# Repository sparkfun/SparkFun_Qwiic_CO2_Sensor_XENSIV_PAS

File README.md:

SparkFun Photoacoustic Spectroscopy CO2 Sensor - PASCO2V01 (Qwiic) 
========================================

[*SparkFun Photoacoustic Spectroscopy CO2 Sensor - PASCO2V01 (Qwiic) (SEN-22956)*](https://www.sparkfun.com/products/22956)

The SparkFun Photoacoustic Spectroscopy CO<sub>2</sub> Sensor features the XENSIV<sup>&trade;</sup> PASCO2V01 sensor package from Infineon<sup>&copy;</sup>. The sensor measures highly-accurate CO<sub>2</sub> data in direct parts-per-million (ppm) format over I<sup>2</sup>C, UART and PWM. The PAS CO2 employs a photoacoustic spectroscopy measurement system that combines narrow-band filtered IR light and a highly sensitive microphone inside the sensing cavity to measure CO<sub>2</sub> concentrations from 0 to 32,000 ppm with a best accuracy of &plusmn;(30ppm + 3%) when reading between 400 ppm and 5,000 ppm. It also includes a microcontroller that converts the data into direct ppm readout over any of the three communication interfaces. The IR emitter on the PAS CO2 requires a 12V supply so the board includes a AP3012 boost regulator with a series of decoupling capacitors to output a clean 12V from the 3.3V sourced through a Qwiic connection.

Repository Contents
-------------------

* **/Documentation** - Data sheets, additional product information
* **/Firmware** - Example code 
* **/Hardware** - Eagle design files (.brd, .sch)
* **/Production** - Production panel files (.brd)
* **/docs** -  Documentation files for the Photoacoustic Spectroscopy CO2 Sensor - PASCO2V01 (Qwiic) 

Documentation
--------------
* **[Library](https://github.com/Infineon/arduino-pas-co2-sensor)** - Arduino library for the XENSIV PAS CO2 Sensor.
* **[Hookup Guide](https://sparkfun.github.io/SparkFun_Qwiic_CO2_Sensor_XENSIV_PAS)** - Basic hookup guide for the Photoacoustic Spectroscopy CO2 Sensor - PASCO2V01 (Qwiic).

Product Versions
----------------
* [SEN-22956](https://www.sparkfun.com/products/22956) - Initial release of the SparkFun Photoacoustic Spectroscopy CO2 Sensor - PASCO2V01 (Qwiic) 

License Information
-------------------

This product is _**open source**_! 

Please review the LICENSE.md file for license information. 

If you have any questions or concerns on licensing, please contact technical support on our [SparkFun forums](https://forum.sparkfun.com/viewforum.php?f=152).

Distributed as-is; no warranty is given.

- Your friends at SparkFun.

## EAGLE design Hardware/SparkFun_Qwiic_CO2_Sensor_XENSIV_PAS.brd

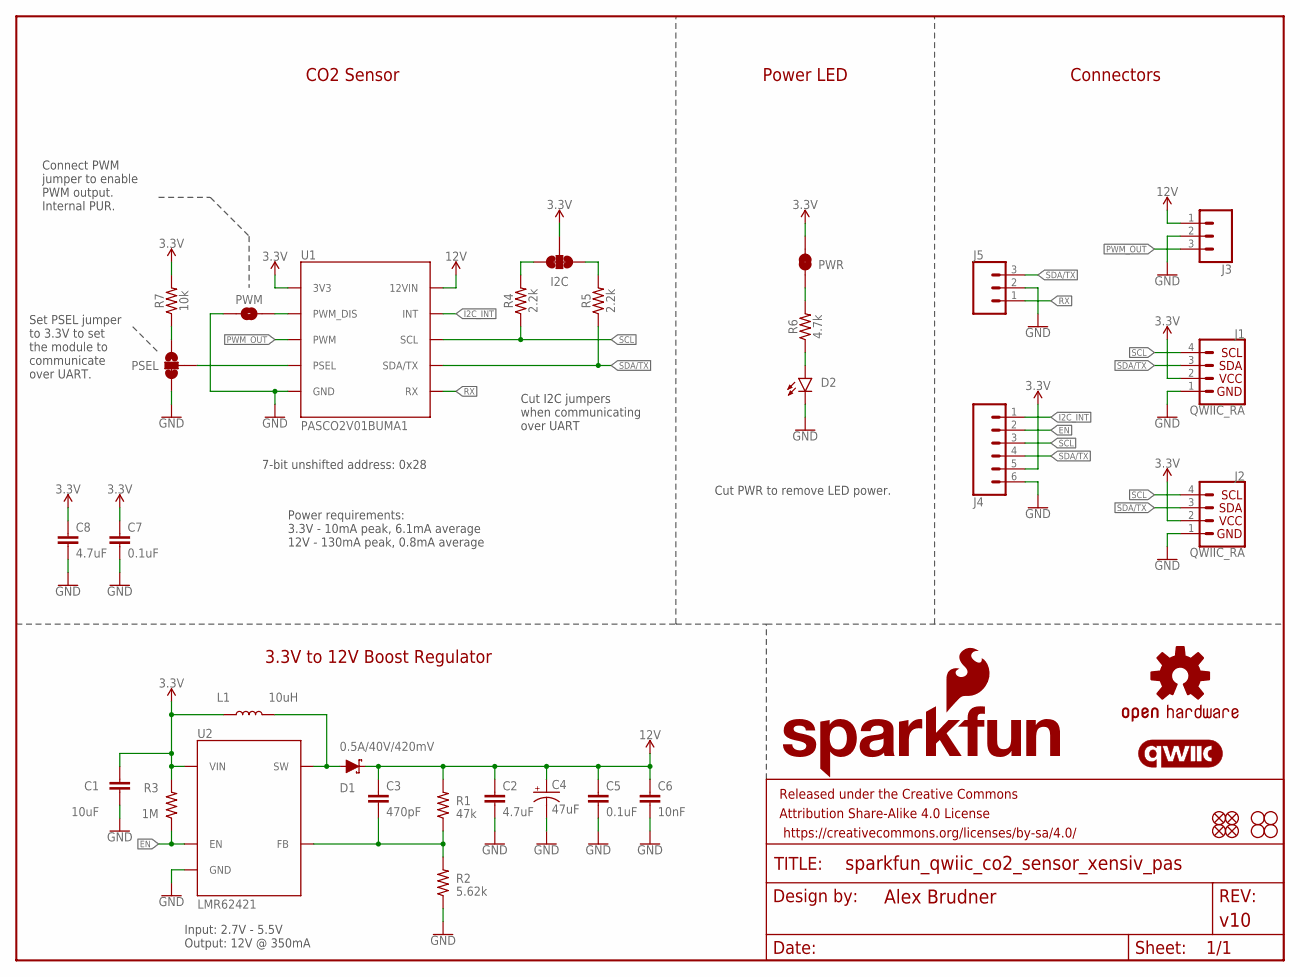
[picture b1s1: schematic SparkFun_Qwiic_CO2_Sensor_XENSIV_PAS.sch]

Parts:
C1: 10uF; 0805
C2, C8: 4.7uF; 0603
C3: 470pF; 0603
C4: 47uF; PANASONIC_D
C5, C7: 0.1uF; 0603
C6: 10nF; 0603
D1: 0.5A/40V/420mV; SOD-323
D2: LED-RED_0603-KB; LED-0603
FD1, FD2, FD3, FD4: FIDUCIALUFIDUCIAL; FIDUCIAL-MICRO
FRAME1: FRAME-LETTER; CREATIVE_COMMONS
H1, H2, H3, H4: STAND-OFF
I2C: JUMPER-SMT_3_2-NC_TRACE_SILK; SMT-JUMPER_3_2-NC_TRACE_SILK
J1, J2: QWIIC_RA; JST04_1MM_RA
J3, J5: CONN_031X03_NO_SILK; 1X03_NO_SILK
J4: CONN_06NO_SILK_NO_POP; 1X06_NO_SILK
L1: 10uH; 0805
LOGO1: SFE_LOGO_NAME_FLAME.1_INCH; SFE_LOGO_NAME_FLAME_.1
LOGO2: QWIIC_LOGO_5MM; QWIIC_5MM
LOGO3: OSHW-LOGOMINI; OSHW-LOGO-MINI
PSEL: JUMPER-SMT_3_1-NC_TRACE_SILK; SMT-JUMPER_3_1-NC_TRACE_SILK
PWM: JUMPER-SMT_2_NO_SILK; SMT-JUMPER_2_NO_SILK
PWR: JUMPER-SMT_2_NC_TRACE_SILK; SMT-JUMPER_2_NC_TRACE_SILK
R1: 47k; 0603
R2: 5.62k; 0603
R3: 1M; 0603
R4, R5: 2.2k; 0603
R6: 4.7k; 0603
R7: 10k; 0603
U1: PASCO2V01BUMA1; LG-MLGA-14-1_Z8B00206105
U2: LMR62421; SOT95P280X145-5M

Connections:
3.3V: C1.1, C7.1, C8.1, I2C.2, J1.2, J2.2, J4.5, L1.1, PWR.2, R3.2, R7.2, U1.1 (3V3), U2.5 (VIN)
12V: C2.1, C3.1, C4.+, C5.1, C6.1, D1.C, J3.1, R1.2, U1.10 (12VIN)
EN: J4.2, R3.1, U2.4 (EN)
GND: C1.2, C2.2, C4.-, C5.2, C6.2, C7.2, C8.2, D2.C, J1.1, J2.1, J3.2, J4.6, J5.2, PSEL.3, PWM.1, R2.1, U1.6 (GND), U1.11 (GND), U1.12 (GND), U1.13 (GND), U1.14 (GND), U2.2 (GND)
I2C_INT: J4.1, U1.7 (INT)
unnamed: I2C.1, R5.2
unnamed: D1.A, L1.2, U2.1 (SW)
unnamed: I2C.3, R4.2
unnamed: C3.2, R1.1, R2.2, U2.3 (FB)
unnamed: PSEL.2, U1.8 (PSEL)
unnamed: D2.A, R6.1
unnamed: PWR.1, R6.2
unnamed: PSEL.1, R7.1
unnamed: PWM.2, U1.5 (PWM_DIS)
PWM_OUT: J3.3, U1.9 (PWM)
RX: J5.1, U1.2 (RX)
SCL: J1.4, J2.4, J4.3, R4.1, U1.3 (SCL)
SDA/TX: J1.3, J2.3, J4.4, J5.3, R5.1, U1.4 (SDA/TX)

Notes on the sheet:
3.3V to 12V Boost Regulator
CO2 Sensor
Connectors
Set PSEL jumper to 3.3V to set the module to communicate over UART.
Cut I2C jumpers when communicating over UART
Power LED
Cut PWR to remove LED power.
Input: 2.7V - 5.5V Output: 12V @ 350mA
7-bit unshifted address: 0x28
Power requirements: 3.3V - 10mA peak, 6.1mA average 12V - 130mA peak, 0.8mA average
Connect PWM jumper to enable PWM output. Internal PUR.

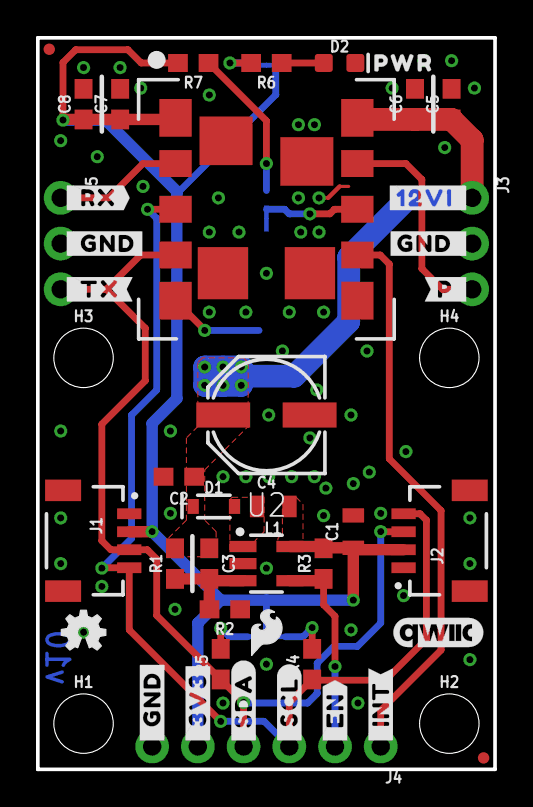
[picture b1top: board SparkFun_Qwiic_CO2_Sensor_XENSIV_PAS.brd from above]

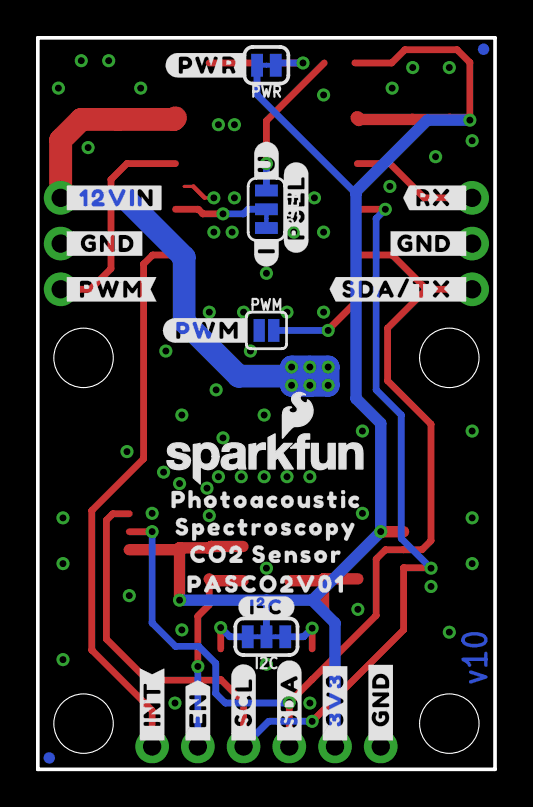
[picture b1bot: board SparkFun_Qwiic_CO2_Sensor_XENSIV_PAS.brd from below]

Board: 2 copper layers, 25.4 x 40.6 mm, 79 parts (30 on the bottom side), 18 nets.

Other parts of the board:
U$1: SFE_LOGO_FLAME_.1
U$2: #_12VIN#0
U$3, U$10: #_EN#0
U$4, U$5: #GND_#0
U$6: #_TX#0
U$7: #_RX#0
U$8, U$9, U$14, U$18: #_GND#0
U$11, U$19: #_3V3#0
U$12: #RX_#0
U$13: #SDA#TX_#0
U$15, U$36: #_SCL#0
U$16: #PWM#0
U$17: #P_#0
U$20, U$35: #_SDA#0
U$21, U$22: #_INT#0
U$24: #PSEL#0
U$25: CO2_SENSOR0
U$26: SFE_LOGO_FLAME_STOP_.1
U$27: #I�C#0
U$28: #PWR#0
U$29: PWR0
U$30: ORDERING_INSTRUCTIONS
U$31: #I#0
U$32: #U#0
U$33: #12VI_#0
U$34: #_PWM#0
U$37: PHOTOACOUSTIC0
U$38: SPECTROSCOPY0
U$39: PASCO2V010

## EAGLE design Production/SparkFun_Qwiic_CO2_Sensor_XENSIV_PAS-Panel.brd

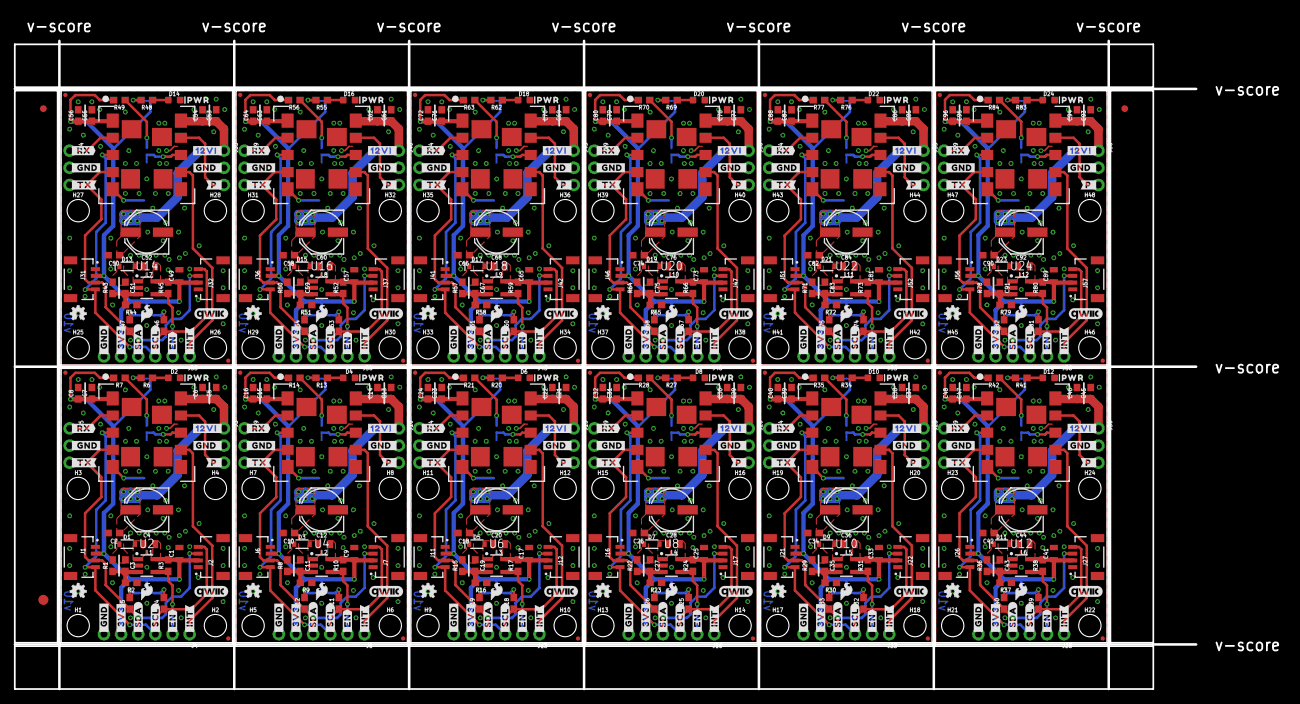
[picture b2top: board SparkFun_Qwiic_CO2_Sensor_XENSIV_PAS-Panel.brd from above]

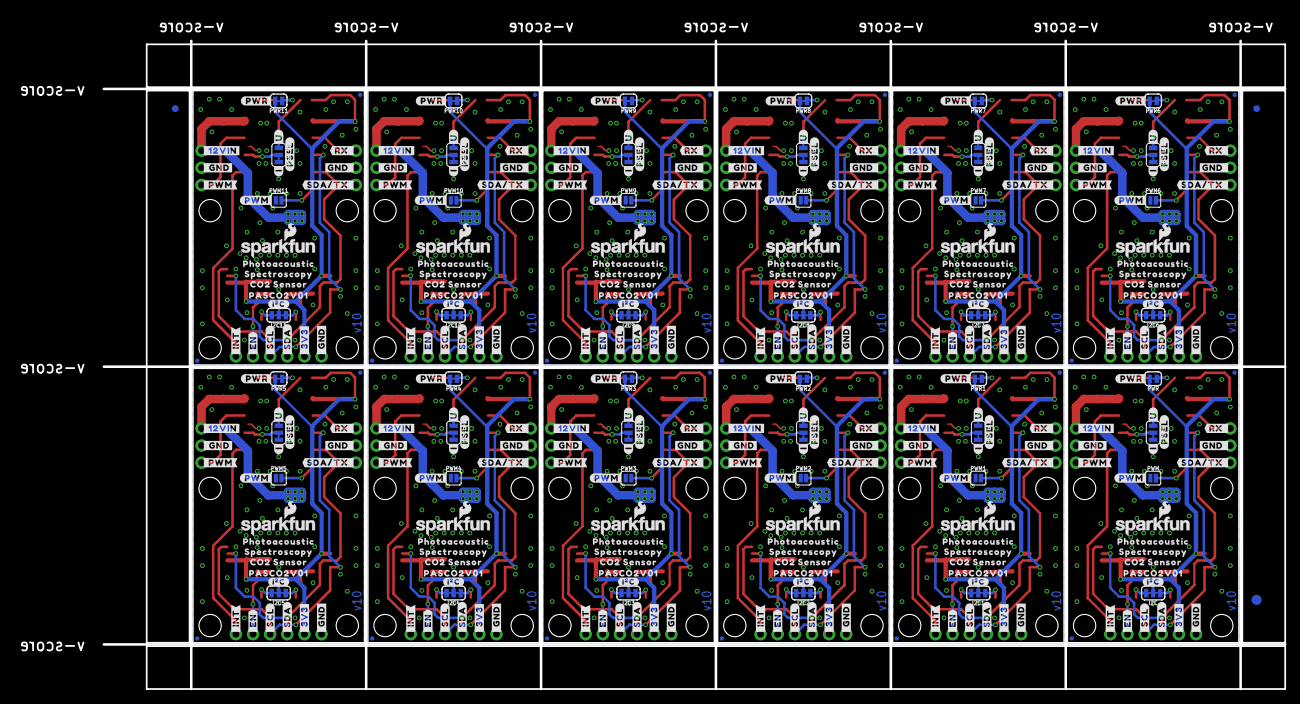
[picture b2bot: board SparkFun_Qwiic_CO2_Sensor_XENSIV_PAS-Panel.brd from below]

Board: 2 copper layers, 188.2 x 99.9 mm, 930 parts (363 on the bottom side), 216 nets.

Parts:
C1, C9, C17, C25, C33, C41, C49, C57, C65, C73, C81, C89: 10uF; 0805
C2, C8, C10, C16, C18, C24, C26, C32, C34, C40, C42, C48, C50, C56, C58, C64, C66, C72, C74, C80, C82, C88, C90, C96: 4.7uF; 0603
C3, C11, C19, C27, C35, C43, C51, C59, C67, C75, C83, C91: 470pF; 0603
C4, C12, C20, C28, C36, C44, C52, C60, C68, C76, C84, C92: 47uF; PANASONIC_D
C5, C7, C13, C15, C21, C23, C29, C31, C37, C39, C45, C47, C53, C55, C61, C63, C69, C71, C77, C79, C85, C87, C93, C95: 0.1uF; 0603
C6, C14, C22, C30, C38, C46, C54, C62, C70, C78, C86, C94: 10nF; 0603
D1, D3, D5, D7, D9, D11, D13, D15, D17, D19, D21, D23: 0.5A/40V/420mV; SOD-323
D2, D4, D6, D8, D10, D12, D14, D16, D18, D20, D22, D24: LED-0603
E$1, E$2, E$3, E$4: FIDUCIAL-1X2
E$5, E$6: FIDUCIAL-1.5X3
FD1, FD2, FD3, FD4, FD5, FD6, FD7, FD8, FD9, FD10, FD11, FD12, FD13, FD14, FD15, FD16, FD17, FD18, FD19, FD20, FD21, FD22, FD23, FD24, FD25, FD26, FD27, FD28, FD29, FD30, FD31, FD32, FD33, FD34, FD35, FD36, FD37, FD38, FD39, FD40, FD41, FD42, FD43, FD44, FD45, FD46, FD47, FD48: FIDUCIALUFIDUCIAL; FIDUCIAL-MICRO
H1, H2, H3, H4, H5, H6, H7, H8, H9, H10, H11, H12, H13, H14, H15, H16, H17, H18, H19, H20, H21, H22, H23, H24, H25, H26, H27, H28, H29, H30, H31, H32, H33, H34, H35, H36, H37, H38, H39, H40, H41, H42, H43, H44, H45, H46, H47, H48: STAND-OFF
I2C, I2C1, I2C2, I2C3, I2C4, I2C5, I2C6, I2C7, I2C8, I2C9, I2C10, I2C11: JUMPER-SMT_3_2-NC_TRACE_SILK; SMT-JUMPER_3_2-NC_TRACE_SILK
J1, J2, J6, J7, J11, J12, J16, J17, J21, J22, J26, J27, J31, J32, J36, J37, J41, J42, J46, J47, J51, J52, J56, J57: QWIIC_RA; JST04_1MM_RA
J3, J5, J9, J10, J14, J15, J19, J20, J24, J25, J29, J30, J34, J35, J39, J40, J44, J45, J49, J50, J54, J55, J59, J60: 1X03_NO_SILK
J4, J8, J13, J18, J23, J28, J33, J38, J43, J48, J53, J58: 1X06_NO_SILK
L1, L2, L3, L4, L5, L6, L7, L8, L9, L10, L11, L12: 10uH; 0805
LOGO1, LOGO4, LOGO7, LOGO10, LOGO13, LOGO16, LOGO19, LOGO22, LOGO25, LOGO28, LOGO31, LOGO34: SFE_LOGO_NAME_FLAME.1_INCH; SFE_LOGO_NAME_FLAME_.1
LOGO2, LOGO5, LOGO8, LOGO11, LOGO14, LOGO17, LOGO20, LOGO23, LOGO26, LOGO29, LOGO32, LOGO35: QWIIC_LOGO_5MM; QWIIC_5MM
LOGO3, LOGO6, LOGO9, LOGO12, LOGO15, LOGO18, LOGO21, LOGO24, LOGO27, LOGO30, LOGO33, LOGO36: OSHW-LOGOMINI; OSHW-LOGO-MINI
PSEL, PSEL1, PSEL2, PSEL3, PSEL4, PSEL5, PSEL6, PSEL7, PSEL8, PSEL9, PSEL10, PSEL11: JUMPER-SMT_3_1-NC_TRACE_SILK; SMT-JUMPER_3_1-NC_TRACE_SILK
PWM, PWM1, PWM2, PWM3, PWM4, PWM5, PWM6, PWM7, PWM8, PWM9, PWM10, PWM11: JUMPER-SMT_2_NO_SILK; SMT-JUMPER_2_NO_SILK
PWR, PWR1, PWR2, PWR3, PWR4, PWR5, PWR6, PWR7, PWR8, PWR9, PWR10, PWR11: JUMPER-SMT_2_NC_TRACE_SILK; SMT-JUMPER_2_NC_TRACE_SILK
R1, R8, R15, R22, R29, R36, R43, R50, R57, R64, R71, R78: 47k; 0603
R2, R9, R16, R23, R30, R37, R44, R51, R58, R65, R72, R79: 5.62k; 0603
R3, R10, R17, R24, R31, R38, R45, R52, R59, R66, R73, R80: 1M; 0603
R4, R5, R11, R12, R18, R19, R25, R26, R32, R33, R39, R40, R46, R47, R53, R54, R60, R61, R67, R68, R74, R75, R81, R82: 2.2k; 0603
R6, R13, R20, R27, R34, R41, R48, R55, R62, R69, R76, R83: 4.7k; 0603
R7, R14, R21, R28, R35, R42, R49, R56, R63, R70, R77, R84: 10k; 0603
U1, U3, U5, U7, U9, U11, U13, U15, U17, U19, U21, U23: PASCO2V01BUMA1; LG-MLGA-14-1_Z8B00206105
U2, U4, U6, U8, U10, U12, U14, U16, U18, U20, U22, U24: LMR62421; SOT95P280X145-5M
U$1, U$23, U$75, U$112, U$149, U$186, U$223, U$260, U$297, U$334, U$371, U$408: SFE_LOGO_FLAME_.1
U$2, U$60, U$97, U$134, U$171, U$208, U$245, U$282, U$319, U$356, U$393, U$430: #_12VIN#0
U$3, U$10, U$61, U$62, U$98, U$99, U$135, U$136, U$172, U$173, U$209, U$210, U$246, U$247, U$283, U$284, U$320, U$321, U$357, U$358, U$394, U$395, U$431, U$432: #_EN#0
U$4, U$5, U$30, U$40, U$76, U$77, U$113, U$114, U$150, U$151, U$187, U$188, U$224, U$225, U$261, U$262, U$298, U$299, U$335, U$336, U$372, U$373, U$409, U$410: #GND_#0
U$6, U$41, U$78, U$115, U$152, U$189, U$226, U$263, U$300, U$337, U$374, U$411: #_TX#0
U$7, U$42, U$79, U$116, U$153, U$190, U$227, U$264, U$301, U$338, U$375, U$412: #_RX#0
U$8, U$9, U$14, U$18, U$43, U$44, U$47, U$49, U$80, U$81, U$84, U$86, U$117, U$118, U$121, U$123, U$154, U$155, U$158, U$160, U$191, U$192, U$195, U$197, U$228, U$229, U$232, U$234, U$265, U$266, U$269, U$271, U$302, U$303, U$306, U$308, U$339, U$340, U$343, U$345, U$376, U$377, U$380, U$382, U$413, U$414, U$417, U$419: #_GND#0
U$11, U$19, U$50, U$63, U$87, U$100, U$124, U$137, U$161, U$174, U$198, U$211, U$235, U$248, U$272, U$285, U$309, U$322, U$346, U$359, U$383, U$396, U$420, U$433: #_3V3#0
U$12, U$45, U$82, U$119, U$156, U$193, U$230, U$267, U$304, U$341, U$378, U$415: #RX_#0
U$13, U$46, U$83, U$120, U$157, U$194, U$231, U$268, U$305, U$342, U$379, U$416: #SDA#TX_#0
U$15, U$36, U$48, U$70, U$85, U$107, U$122, U$144, U$159, U$181, U$196, U$218, U$233, U$255, U$270, U$292, U$307, U$329, U$344, U$366, U$381, U$403, U$418, U$440: #_SCL#0
U$16, U$66, U$103, U$140, U$177, U$214, U$251, U$288, U$325, U$362, U$399, U$436: #PWM#0
U$17, U$64, U$101, U$138, U$175, U$212, U$249, U$286, U$323, U$360, U$397, U$434: #P_#0
U$20, U$35, U$68, U$69, U$105, U$106, U$142, U$143, U$179, U$180, U$216, U$217, U$253, U$254, U$290, U$291, U$327, U$328, U$364, U$365, U$401, U$402, U$438, U$439: #_SDA#0
U$21, U$22, U$51, U$52, U$88, U$89, U$125, U$126, U$162, U$163, U$199, U$200, U$236, U$237, U$273, U$274, U$310, U$311, U$347, U$348, U$384, U$385, U$421, U$422: #_INT#0
U$24, U$53, U$90, U$127, U$164, U$201, U$238, U$275, U$312, U$349, U$386, U$423: #PSEL#0
U$25, U$73, U$110, U$147, U$184, U$221, U$258, U$295, U$332, U$369, U$406, U$443: CO2_SENSOR0
U$26, U$55, U$92, U$129, U$166, U$203, U$240, U$277, U$314, U$351, U$388, U$425: SFE_LOGO_FLAME_STOP_.1
U$27, U$54, U$91, U$128, U$165, U$202, U$239, U$276, U$313, U$350, U$387, U$424: #I�C#0
U$28, U$67, U$104, U$141, U$178, U$215, U$252, U$289, U$326, U$363, U$400, U$437: #PWR#0
U$29, U$56, U$93, U$130, U$167, U$204, U$241, U$278, U$315, U$352, U$389, U$426: PWR0
U$31, U$58, U$95, U$132, U$169, U$206, U$243, U$280, U$317, U$354, U$391, U$428: #I#0
U$32, U$57, U$94, U$131, U$168, U$205, U$242, U$279, U$316, U$353, U$390, U$427: #U#0
U$33, U$59, U$96, U$133, U$170, U$207, U$244, U$281, U$318, U$355, U$392, U$429: #12VI_#0
U$34, U$65, U$102, U$139, U$176, U$213, U$250, U$287, U$324, U$361, U$398, U$435: #_PWM#0
U$37, U$71, U$108, U$145, U$182, U$219, U$256, U$293, U$330, U$367, U$404, U$441: PHOTOACOUSTIC0
U$38, U$72, U$109, U$146, U$183, U$220, U$257, U$294, U$331, U$368, U$405, U$442: SPECTROSCOPY0
U$39, U$74, U$111, U$148, U$185, U$222, U$259, U$296, U$333, U$370, U$407, U$444: PASCO2V010

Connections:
3.3V: C1.1, C7.1, C8.1, I2C.2, J1.2, J2.2, J4.5, L1.1, PWR.2, R3.2, R7.2, U1.1, U2.5
3.3V1: C9.1, C15.1, C16.1, I2C1.2, J6.2, J7.2, J8.5, L2.1, PWR1.2, R10.2, R14.2, U3.1, U4.5
3.3V2: C17.1, C23.1, C24.1, I2C2.2, J11.2, J12.2, J13.5, L3.1, PWR2.2, R17.2, R21.2, U5.1, U6.5
3.3V3: C25.1, C31.1, C32.1, I2C3.2, J16.2, J17.2, J18.5, L4.1, PWR3.2, R24.2, R28.2, U7.1, U8.5
3.3V4: C33.1, C39.1, C40.1, I2C4.2, J21.2, J22.2, J23.5, L5.1, PWR4.2, R31.2, R35.2, U9.1, U10.5
3.3V5: C41.1, C47.1, C48.1, I2C5.2, J26.2, J27.2, J28.5, L6.1, PWR5.2, R38.2, R42.2, U11.1, U12.5
3.3V6: C49.1, C55.1, C56.1, I2C6.2, J31.2, J32.2, J33.5, L7.1, PWR6.2, R45.2, R49.2, U13.1, U14.5
3.3V7: C57.1, C63.1, C64.1, I2C7.2, J36.2, J37.2, J38.5, L8.1, PWR7.2, R52.2, R56.2, U15.1, U16.5
3.3V8: C65.1, C71.1, C72.1, I2C8.2, J41.2, J42.2, J43.5, L9.1, PWR8.2, R59.2, R63.2, U17.1, U18.5
3.3V9: C73.1, C79.1, C80.1, I2C9.2, J46.2, J47.2, J48.5, L10.1, PWR9.2, R66.2, R70.2, U19.1, U20.5
3.3V10: C81.1, C87.1, C88.1, I2C10.2, J51.2, J52.2, J53.5, L11.1, PWR10.2, R73.2, R77.2, U21.1, U22.5
3.3V11: C89.1, C95.1, C96.1, I2C11.2, J56.2, J57.2, J58.5, L12.1, PWR11.2, R80.2, R84.2, U23.1, U24.5
12V: C2.1, C3.1, C4.+, C5.1, C6.1, D1.C, J3.1, R1.2, U1.10
12V1: C10.1, C11.1, C12.+, C13.1, C14.1, D3.C, J10.1, R8.2, U3.10
12V2: C18.1, C19.1, C20.+, C21.1, C22.1, D5.C, J15.1, R15.2, U5.10
12V3: C26.1, C27.1, C28.+, C29.1, C30.1, D7.C, J20.1, R22.2, U7.10
12V4: C34.1, C35.1, C36.+, C37.1, C38.1, D9.C, J25.1, R29.2, U9.10
12V5: C42.1, C43.1, C44.+, C45.1, C46.1, D11.C, J30.1, R36.2, U11.10
12V6: C50.1, C51.1, C52.+, C53.1, C54.1, D13.C, J35.1, R43.2, U13.10
12V7: C58.1, C59.1, C60.+, C61.1, C62.1, D15.C, J40.1, R50.2, U15.10
12V8: C66.1, C67.1, C68.+, C69.1, C70.1, D17.C, J45.1, R57.2, U17.10
12V9: C74.1, C75.1, C76.+, C77.1, C78.1, D19.C, J50.1, R64.2, U19.10
12V10: C82.1, C83.1, C84.+, C85.1, C86.1, D21.C, J55.1, R71.2, U21.10
12V11: C90.1, C91.1, C92.+, C93.1, C94.1, D23.C, J60.1, R78.2, U23.10
EN: J4.2, R3.1, U2.4
EN1: J8.2, R10.1, U4.4
EN2: J13.2, R17.1, U6.4
EN3: J18.2, R24.1, U8.4
EN4: J23.2, R31.1, U10.4
EN5: J28.2, R38.1, U12.4
EN6: J33.2, R45.1, U14.4
EN7: J38.2, R52.1, U16.4
EN8: J43.2, R59.1, U18.4
EN9: J48.2, R66.1, U20.4
EN10: J53.2, R73.1, U22.4
EN11: J58.2, R80.1, U24.4
GND: C1.2, C2.2, C4.-, C5.2, C6.2, C7.2, C8.2, D2.C, J1.1, J2.1, J3.2, J4.6, J5.2, PSEL.3, PWM.1, R2.1, U1.6, U1.11, U1.12, U1.13, U1.14, U2.2
GND1: C9.2, C10.2, C12.-, C13.2, C14.2, C15.2, C16.2, D4.C, J6.1, J7.1, J8.6, J9.2, J10.2, PSEL1.3, PWM1.1, R9.1, U3.6, U3.11, U3.12, U3.13, U3.14, U4.2
GND2: C17.2, C18.2, C20.-, C21.2, C22.2, C23.2, C24.2, D6.C, J11.1, J12.1, J13.6, J14.2, J15.2, PSEL2.3, PWM2.1, R16.1, U5.6, U5.11, U5.12, U5.13, U5.14, U6.2
GND3: C25.2, C26.2, C28.-, C29.2, C30.2, C31.2, C32.2, D8.C, J16.1, J17.1, J18.6, J19.2, J20.2, PSEL3.3, PWM3.1, R23.1, U7.6, U7.11, U7.12, U7.13, U7.14, U8.2
GND4: C33.2, C34.2, C36.-, C37.2, C38.2, C39.2, C40.2, D10.C, J21.1, J22.1, J23.6, J24.2, J25.2, PSEL4.3, PWM4.1, R30.1, U9.6, U9.11, U9.12, U9.13, U9.14, U10.2
GND5: C41.2, C42.2, C44.-, C45.2, C46.2, C47.2, C48.2, D12.C, J26.1, J27.1, J28.6, J29.2, J30.2, PSEL5.3, PWM5.1, R37.1, U11.6, U11.11, U11.12, U11.13, U11.14, U12.2
GND6: C49.2, C50.2, C52.-, C53.2, C54.2, C55.2, C56.2, D14.C, J31.1, J32.1, J33.6, J34.2, J35.2, PSEL6.3, PWM6.1, R44.1, U13.6, U13.11, U13.12, U13.13, U13.14, U14.2
GND7: C57.2, C58.2, C60.-, C61.2, C62.2, C63.2, C64.2, D16.C, J36.1, J37.1, J38.6, J39.2, J40.2, PSEL7.3, PWM7.1, R51.1, U15.6, U15.11, U15.12, U15.13, U15.14, U16.2
GND8: C65.2, C66.2, C68.-, C69.2, C70.2, C71.2, C72.2, D18.C, J41.1, J42.1, J43.6, J44.2, J45.2, PSEL8.3, PWM8.1, R58.1, U17.6, U17.11, U17.12, U17.13, U17.14, U18.2
GND9: C73.2, C74.2, C76.-, C77.2, C78.2, C79.2, C80.2, D20.C, J46.1, J47.1, J48.6, J49.2, J50.2, PSEL9.3, PWM9.1, R65.1, U19.6, U19.11, U19.12, U19.13, U19.14, U20.2
GND10: C81.2, C82.2, C84.-, C85.2, C86.2, C87.2, C88.2, D22.C, J51.1, J52.1, J53.6, J54.2, J55.2, PSEL10.3, PWM10.1, R72.1, U21.6, U21.11, U21.12, U21.13, U21.14, U22.2
GND11: C89.2, C90.2, C92.-, C93.2, C94.2, C95.2, C96.2, D24.C, J56.1, J57.1, J58.6, J59.2, J60.2, PSEL11.3, PWM11.1, R79.1, U23.6, U23.11, U23.12, U23.13, U23.14, U24.2
I2C_INT: J4.1, U1.7
I2C_INT1: J8.1, U3.7
I2C_INT2: J13.1, U5.7
I2C_INT3: J18.1, U7.7
I2C_INT4: J23.1, U9.7
I2C_INT5: J28.1, U11.7
I2C_INT6: J33.1, U13.7
I2C_INT7: J38.1, U15.7
I2C_INT8: J43.1, U17.7
I2C_INT9: J48.1, U19.7
I2C_INT10: J53.1, U21.7
I2C_INT11: J58.1, U23.7
unnamed: I2C.1, R5.2
unnamed: D1.A, L1.2, U2.1
unnamed: I2C.3, R4.2
unnamed: C3.2, R1.1, R2.2, U2.3
unnamed: PSEL.2, U1.8
unnamed: D2.A, R6.1
unnamed: PWR.1, R6.2
unnamed: PSEL.1, R7.1
unnamed: PWM.2, U1.5
unnamed: D3.A, L2.2, U4.1
unnamed: C11.2, R8.1, R9.2, U4.3
unnamed: I2C1.1, R12.2
unnamed: I2C1.3, R11.2
unnamed: PSEL1.2, U3.8
unnamed: D4.A, R13.1
unnamed: PWR1.1, R13.2
unnamed: PSEL1.1, R14.1
unnamed: PWM1.2, U3.5
unnamed: D5.A, L3.2, U6.1
unnamed: C19.2, R15.1, R16.2, U6.3
unnamed: I2C2.1, R19.2
unnamed: I2C2.3, R18.2
unnamed: PSEL2.2, U5.8
unnamed: D6.A, R20.1
unnamed: PWR2.1, R20.2
unnamed: PSEL2.1, R21.1
unnamed: PWM2.2, U5.5
unnamed: D7.A, L4.2, U8.1
unnamed: C27.2, R22.1, R23.2, U8.3
unnamed: I2C3.1, R26.2
unnamed: I2C3.3, R25.2
unnamed: PSEL3.2, U7.8
unnamed: D8.A, R27.1
unnamed: PWR3.1, R27.2
unnamed: PSEL3.1, R28.1
unnamed: PWM3.2, U7.5
unnamed: D9.A, L5.2, U10.1
unnamed: C35.2, R29.1, R30.2, U10.3
unnamed: I2C4.1, R33.2
unnamed: I2C4.3, R32.2
unnamed: PSEL4.2, U9.8
unnamed: D10.A, R34.1
unnamed: PWR4.1, R34.2
unnamed: PSEL4.1, R35.1
unnamed: PWM4.2, U9.5
unnamed: D11.A, L6.2, U12.1
unnamed: C43.2, R36.1, R37.2, U12.3
unnamed: I2C5.1, R40.2
unnamed: I2C5.3, R39.2
unnamed: PSEL5.2, U11.8
unnamed: D12.A, R41.1
unnamed: PWR5.1, R41.2
unnamed: PSEL5.1, R42.1
unnamed: PWM5.2, U11.5
unnamed: D13.A, L7.2, U14.1
unnamed: C51.2, R43.1, R44.2, U14.3
unnamed: I2C6.1, R47.2
unnamed: I2C6.3, R46.2
unnamed: PSEL6.2, U13.8
unnamed: D14.A, R48.1
unnamed: PWR6.1, R48.2
unnamed: PSEL6.1, R49.1
unnamed: PWM6.2, U13.5
unnamed: D15.A, L8.2, U16.1
unnamed: C59.2, R50.1, R51.2, U16.3
unnamed: I2C7.1, R54.2
unnamed: I2C7.3, R53.2
unnamed: PSEL7.2, U15.8
unnamed: D16.A, R55.1
unnamed: PWR7.1, R55.2
unnamed: PSEL7.1, R56.1
unnamed: PWM7.2, U15.5
unnamed: D17.A, L9.2, U18.1
unnamed: C67.2, R57.1, R58.2, U18.3
unnamed: I2C8.1, R61.2
unnamed: I2C8.3, R60.2
unnamed: PSEL8.2, U17.8
unnamed: D18.A, R62.1
unnamed: PWR8.1, R62.2
unnamed: PSEL8.1, R63.1
unnamed: PWM8.2, U17.5
unnamed: D19.A, L10.2, U20.1
unnamed: C75.2, R64.1, R65.2, U20.3
unnamed: I2C9.1, R68.2
unnamed: I2C9.3, R67.2
unnamed: PSEL9.2, U19.8
unnamed: D20.A, R69.1
unnamed: PWR9.1, R69.2
unnamed: PSEL9.1, R70.1
unnamed: PWM9.2, U19.5
unnamed: D21.A, L11.2, U22.1
unnamed: C83.2, R71.1, R72.2, U22.3
unnamed: I2C10.1, R75.2
unnamed: I2C10.3, R74.2
unnamed: PSEL10.2, U21.8
unnamed: D22.A, R76.1
unnamed: PWR10.1, R76.2
unnamed: PSEL10.1, R77.1
unnamed: PWM10.2, U21.5
unnamed: D23.A, L12.2, U24.1
unnamed: C91.2, R78.1, R79.2, U24.3
unnamed: I2C11.1, R82.2
unnamed: I2C11.3, R81.2
unnamed: PSEL11.2, U23.8
unnamed: D24.A, R83.1
unnamed: PWR11.1, R83.2
unnamed: PSEL11.1, R84.1
unnamed: PWM11.2, U23.5
PWM_OUT: J3.3, U1.9
PWM_OUT1: J10.3, U3.9
PWM_OUT2: J15.3, U5.9
PWM_OUT3: J20.3, U7.9
PWM_OUT4: J25.3, U9.9
PWM_OUT5: J30.3, U11.9
PWM_OUT6: J35.3, U13.9
PWM_OUT7: J40.3, U15.9
PWM_OUT8: J45.3, U17.9
PWM_OUT9: J50.3, U19.9
PWM_OUT10: J55.3, U21.9
PWM_OUT11: J60.3, U23.9
RX: J5.1, U1.2
RX1: J9.1, U3.2
RX2: J14.1, U5.2
RX3: J19.1, U7.2
RX4: J24.1, U9.2
RX5: J29.1, U11.2
RX6: J34.1, U13.2
RX7: J39.1, U15.2
RX8: J44.1, U17.2
RX9: J49.1, U19.2
RX10: J54.1, U21.2
RX11: J59.1, U23.2
SCL: J1.4, J2.4, J4.3, R4.1, U1.3
SCL1: J6.4, J7.4, J8.3, R11.1, U3.3
SCL2: J11.4, J12.4, J13.3, R18.1, U5.3
SCL3: J16.4, J17.4, J18.3, R25.1, U7.3
SCL4: J21.4, J22.4, J23.3, R32.1, U9.3
SCL5: J26.4, J27.4, J28.3, R39.1, U11.3
SCL6: J31.4, J32.4, J33.3, R46.1, U13.3
SCL7: J36.4, J37.4, J38.3, R53.1, U15.3
SCL8: J41.4, J42.4, J43.3, R60.1, U17.3
SCL9: J46.4, J47.4, J48.3, R67.1, U19.3
SCL10: J51.4, J52.4, J53.3, R74.1, U21.3
SCL11: J56.4, J57.4, J58.3, R81.1, U23.3
SDA/TX: J1.3, J2.3, J4.4, J5.3, R5.1, U1.4
SDA/TX1: J6.3, J7.3, J8.4, J9.3, R12.1, U3.4
SDA/TX2: J11.3, J12.3, J13.4, J14.3, R19.1, U5.4
SDA/TX3: J16.3, J17.3, J18.4, J19.3, R26.1, U7.4
SDA/TX4: J21.3, J22.3, J23.4, J24.3, R33.1, U9.4
SDA/TX5: J26.3, J27.3, J28.4, J29.3, R40.1, U11.4
SDA/TX6: J31.3, J32.3, J33.4, J34.3, R47.1, U13.4
SDA/TX7: J36.3, J37.3, J38.4, J39.3, R54.1, U15.4
SDA/TX8: J41.3, J42.3, J43.4, J44.3, R61.1, U17.4
SDA/TX9: J46.3, J47.3, J48.4, J49.3, R68.1, U19.4
SDA/TX10: J51.3, J52.3, J53.4, J54.3, R75.1, U21.4
SDA/TX11: J56.3, J57.3, J58.4, J59.3, R82.1, U23.4

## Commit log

2023-07-07 Add documentation.
2023-07-07 Added v01 files.
2023-07-10 Update pre design review
    Add keepouts for exposed pads.
    Move vias to avoid keepouts.
    Add 10k PUR to PSEL 3.3V selector.
    Add voltage/current details to CO2 sensor on schematic.
    Modified bottom PTHs to match standard order.
    Move vias for ground pour.
2023-07-10 Update ordering instructions.
2023-07-10 Post design review changes and gerbers.
    Add tDocu for the can and put squares for PnP.
    Move EN to bottom row.
    Rearrange I2C PTHs on bottom row to align with prior art.
    Add PWM/PWM_DIS breakout.
    Change silk on 12V to 12VIN.
    Shift vertical PTHs down 0.05 to line up with perfboard holes.
2023-07-31 Update xensiv_pas.lbr
    Add proper PROD_ID
2023-07-31 Update for v10.
    Schematic - Make version v10.
    Board - Make version v10. Change size of Silk title text.
    Production - Removed individual board gerbers, add panel gerbers.
2023-08-01 Move Flame silk to middle.
    Repanelize after.
2023-08-11 Initial Docs commit
    Adding mkdocs page build files and initial Hookup Guide pages.
2023-08-16 Docs update
    Updates to Hardware Overview, Hardware Assembly & Troubleshooting
2023-08-22 Docs Update
    Adding examples section basics & minor updates to Assembly & Overview sections.
2023-08-30 Swapped boost regulator.
2023-09-20 BOM change and add logo to silk.
2023-10-06 Add Early Measurement example
    Add corresponding app note.
2023-10-17 Docs Update
    Docs update with minor content tweaks & photos added.
2023-10-23 Add calibration document.
2023-10-23 Update README.md
    Updating readme from template for product release.
2023-10-25 Update docs
    Adding calibration information and other minor updates for release.
2023-10-25 Update workflows
    Adding mkdocs.yml and workflows folder
2023-10-25 Update README.md
    Update product photo with correct size.
2023-10-31 Update hardware_overview.md
    Adding missing I2C jumper description.
2023-10-31 Update hardware_overview.md
    Typo fix
2023-11-02 Update introduction
    Adding embedded product video & formatting.
2023-11-02 Deployed 0e8fc4b with MkDocs version: 1.5.3
2024-10-25 Update mkdocs.yml
    Analytics update.
2024-10-25 Deployed 9aa030a with MkDocs version: 1.6.1
2025-02-20 Deployed 08a65f0 with MkDocs version: 1.6.1

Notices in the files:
parts and their libraries:
SparkFun-Aesthetics: Licensing: Creative Commons ShareAlike 4.0 International - https://creativecommons.org/licenses/by-sa/4.0
SparkFun-Aesthetics: Released under the Creative Commons Attribution Share-Alike 4.0 License
SparkFun-Aesthetics: https://creativecommons.org/licenses/by-sa/4.0
